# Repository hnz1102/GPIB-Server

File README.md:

<div align="center">
  <h1><code>GPIB Server</code></h1>
  <p>SSH / Web controlled IEEE-488 (GPIB) controller on a single ESP32-S3</p>
  
</div>

# gpib-server — SSH-to-GPIB Bridge for ESP32-S3

Firmware for the ESP32-S3 **GPIB-Server** board. It drives an IEEE-488 (GPIB)
bus directly from GPIO through SN75160B / SN75161B bus transceivers. Measuring
instruments can be controlled over Wi-Fi with an **SSH** session or the
**browser terminal**, using **Prologix-compatible** `++` commands.

It is written in Rust (esp-idf-hal / esp-idf-svc), with a C component (wolfSSH)
for the SSH server. It is derived from
[ssh-serial-bridge](#release-history) v0.1.2.

## Features

| Feature | Description |
|---------|-------------|
| GPIB controller | System controller / controller-in-charge on the GPIB bus (IFC, REN, ATN, SRQ, serial poll, SDC, GET, GTL, LLO) |
| Prologix-compatible commands | `++addr`, `++read`, `++auto`, `++eos`, `++eoi`, `++spoll`, `++clr`, `++trg` … (controller mode) |
| SSH server | Port 22, password authentication via wolfSSH, interactive (`gpib`) and script (`gpib raw`) modes |
| WebSocket terminal | Built-in xterm.js GPIB terminal at `/terminal` |
| Spectrum view | Real-time trace display of an ADVANTEST R3267 (R3200 series) spectrum analyzer at `/spectrum` (binary capture on the ESP32, ~13 frames/s) |
| Power supply page | Control and monitoring of an HP / Agilent 6612B (SCPI) DC power supply at `/psu`: output, set values, protection, trend chart, CSV |
| Multimeter page | HP / Agilent 34401A digital multimeter at `/dmm`: function, range, resolution, null, statistics, trend chart, CSV |
| Web UI | Browser-based configuration and device status (GPIB address, SRQ, SSH sessions) |
| Mini display | SSD1306 128×64 OLED (I2C): Wi-Fi, IP, GPIB address, chip temperature |
| WPS support | Wi-Fi Protected Setup (PBC mode) |
| OTA update | `ssh … update < app.bin` with automatic rollback |
| UDP Syslog | RFC 5424 remote logging over UDP |
| NTP | Time synchronisation on boot; up to 4 servers |
| NVS settings | Persistent configuration stored in NVS; editable via Web UI at runtime |

---

## Screenshots

<table>
<tr>
<td align="center" width="50%"><br><b>Main menu</b> (<code>/</code>)</td>
<td align="center" width="50%"><br><b>GPIB terminal</b> (<code>/terminal</code>)</td>
</tr>
<tr>
<td align="center"><br><b>DC power supply</b>, HP 6612B (<code>/psu</code>)</td>
<td align="center"><br><b>Digital multimeter</b>, HP 34401A (<code>/dmm</code>)</td>
</tr>
<tr>
<td align="center"><br><b>Status</b> (<code>/status</code>)</td>
<td align="center"><br><b>Configuration</b> (<code>/config</code>)</td>
</tr>
<tr>
<td align="center" colspan="2"><br><b>Login</b> (<code>/login</code>)</td>
</tr>
</table>

The power supply and multimeter screenshots were taken with simulated instrument
replies; the other pages show the live device (Wi-Fi name and passwords replaced).

## Release History

### v0.1.0 (gpib-server)

- First GPIB-Server release, derived from ssh-serial-bridge v0.1.2.
- Added the GPIB controller driver and the Prologix-compatible command interpreter (`src/gpib.rs`).
- Added the SSH `gpib` / `gpib raw` commands and the browser GPIB terminal.
- Removed UART (COM1/COM2), USB CDC host, GPIO/PWM outputs, SPI display, ADC / power detection and the related SSH commands (`console usbN/comN`, `power`, `dcpower`, `powercycle`, `pwm`).
- Moved the mini display SDA to GPIO13.
- The console log now goes to USB-C (USB-Serial-JTAG).

---

## Architecture

```
SSH client ──[TCP:22]──► ssh_bridge.c (wolfSSH)
                               │  per-session ring buffers (PSRAM)
                               ▼
                        bridge.rs (SSH / WebSocket glue)
                               │
Browser ──[HTTP/WS]──► httpserver.rs ──► gpib.rs
 ├── /          (configuration page)      ├── Prologix-compatible interpreter (worker thread)
 └── /terminal  (xterm.js + /ws/serial)   └── GPIB bus driver (GPIO, 3-wire handshake)
                                                 │
                         SN74LVC245A ×2 ── SN75160B / SN75161B ── GPIB connector
```

---

## Hardware

<table>
<tr>
<td align="center" width="33%"><br><b>PCB</b>: SN75160B / SN75161B transceivers, SN74LVC245A buffers, USB-C, BOOT/CFG button and SSD1306 OLED; the IEEE-488 connector is on the back</td>
<td align="center" width="33%"><br><b>Case</b> (3D-printed): USB-C power on the left, GPIB connector on the right</td>
<td align="center" width="33%"><br><b>Mini display</b>: Wi-Fi RSSI, IP address, GPIB address and chip temperature</td>
</tr>
</table>

### Case (3D printing)

| File | Part | Size (W × D × H) |
|------|------|------------------|
| [`hw/body.stl`](hw/body.stl) | Body | 86 × 67 × 25 mm |
| [`hw/upper.stl`](hw/upper.stl) | Upper part | 91 × 76 × 27 mm |

Sizes are the bounding boxes of the STL files.

The schematic is in [`hw/GPIB-Server.kicad_sch`](hw/GPIB-Server.kicad_sch) ([PDF](hw/schematic.pdf)). For the
design rationale (level translation, direction control and pull-ups), see
[`doc/gpib-hardware.md`](doc/gpib-hardware.md).

| Ref | Part | Function |
|-----|------|----------|
| U1 | ESP32-S3-WROOM-1-N16R8 | MCU (16 MB flash, 8 MB octal PSRAM) |
| U2 | AZ1117-3.3 | 5 V (USB VBUS) → 3.3 V LDO |
| U3 | SSD1306 module | 128×64 OLED (I2C) |
| U4 | SN74LVC245A | DIO1–8 buffer (3.3 V, 5 V-tolerant) |
| U5 | SN74LVC245A | DAV / EOI / NRFD / NDAC buffer (NRFD/NDAC wired B→A reversed) |
| U6 | SN74LVC1G34 | SRQ input buffer |
| U7 | SN75160B | GPIB data transceiver (5 V) |
| U8 | SN75161B | GPIB management transceiver (5 V, DC = GND → system controller) |
| J1 | USB-C (device) | 5 V power, flashing and console (USB-Serial-JTAG) |
| J2 | IEEE-488 24-pin | GPIB connector |

### Pin Assignment

| GPIO | Signal | Direction (ESP32 side) | Path |
|------|--------|------------------------|------|
| 4–11 | DIO1–DIO8 | bidirectional (TE) | U4 → U7 |
| 15 | DAV  | bidirectional (same as TE) | U5 A1/B1 → U8 |
| 18 | EOI  | bidirectional (same as TE) | U5 A2/B2 → U8 |
| 16 | NRFD | bidirectional (inverse of TE) | U5 B3/A3 (reversed) → U8 |
| 17 | NDAC | bidirectional (inverse of TE) | U5 B4/A4 (reversed) → U8 |
| 21 | ATN  | output | 1 kΩ → U8 |
| 38 | REN  | output | 1 kΩ → U8 |
| 39 | IFC  | output | 1 kΩ → U8 |
| 40 | SRQ  | input  | U8 → U6 |
| 12 | TE   | output (direction: H = talk) | U7/U8 TE, U4/U5 DIR (10 kΩ pull-down) |
| 2  | OE#  | output (LVC245A enable, active low) | U4/U5 OE (10 kΩ pull-up) |
| 13 | I2C SDA | — | OLED |
| 3  | I2C SCL | — | OLED |
| 0  | BOOT button | input | Long press (≥ 10 s): factory reset |
| 46 | (strap) | — | 10 kΩ pull-down (download mode works with the BOOT button) |
| 19 / 20 | USB D− / D+ | — | USB-C (USB-Serial-JTAG) |

The GPIB bus uses negative logic: a LOW level means asserted, and a data bit of 1
is driven LOW. The firmware handles the inversion.

### Button

| GPIO | Function |
|------|----------|
| 0 (BOOT) | Long press (≥ 10 s): erase NVS and restore `cfg.toml` defaults. A countdown is shown on the mini display from 5 s onwards. |

---

## Directory Layout

```
gpib-server/
├── src/
│   ├── main.rs           # Entry point, peripheral initialisation
│   ├── gpib.rs           # GPIB bus driver + Prologix-compatible interpreter
│   ├── bridge.rs         # SSH (C component) / WebSocket ⇄ GPIB glue
│   ├── httpserver.rs     # HTTP/WebSocket server, NVS config management
│   ├── wifi.rs           # Wi-Fi STA connection (DHCP / static IP / WPS)
│   ├── mini_display.rs   # SSD1306 status display
│   ├── syslogger.rs      # UDP Syslog logger (RFC 5424)
│   ├── btn_ctrl.rs       # GPIO0 button (long press: factory reset)
│   └── boot_log.rs       # NVS boot counter and rolling reset-reason log
├── components/
│   ├── ssh_bridge/       # SSH server C component (wolfSSH wrapper)
│   ├── wolfssh/          # wolfSSH (github.com/wolfSSL/wolfssh, commit 157cb01f)
│   └── wolfssl/          # wolfSSL/wolfCrypt (github.com/wolfSSL/wolfssl, commit b7e7e755)
├── doc/gpib-hardware.md  # Hardware design notes (pin list, connections, rules)
├── hw/
│   ├── GPIB-Server.kicad_* # KiCad project, schematic and PCB
│   ├── schematic.pdf     # Schematic (PDF)
│   ├── production/       # Gerber (zip), BOM, positions, netlist for PCB assembly
│   ├── body.stl          # Case: body (3D printing)
│   └── upper.stl         # Case: upper part (3D printing)
├── static/               # Embedded pages and files (menu, status, spectrum, psu, dmm; xterm.js (gzip) / css / fit addon)
├── cfg.toml.example      # Template for cfg.toml (build-time defaults; cfg.toml itself is not in git)
├── sdkconfig.defaults    # ESP-IDF build settings
├── partitions.csv        # Flash partition table
├── setup_components.sh   # Initial setup script for components/
└── setup_env.sh          # One-shot environment setup (Rust, espup, udev)
```

---

## Configuration

### cfg.toml (build-time defaults)

Copy `cfg.toml.example` to `cfg.toml` and edit it for your environment before
building (`cfg.toml` holds credentials and is ignored by git). The section name must
match the crate name (`gpib-server`).

```toml
[gpib-server]
wps_enable     = "true"     # "true": use WPS PBC on next boot when SSID is empty
wifi_ssid      = "your-ssid"
wifi_psk       = "your-password"
ip_mode        = "dhcp"           # "dhcp" or "static"
ip_address     = "192.168.0.200"
subnet_mask    = "255.255.255.0"
gateway        = "192.168.0.1"
dns            = "1.1.1.1"

syslog_server    = "192.168.0.140:514"
syslog_enable    = "false"
syslog_host_name = "gpib-server"
syslog_app_name  = "gpib-server"

ssh_user     = "admin"
ssh_password = "gpibpass"

# NTP servers (up to 4, in priority order)
ntp_server1 = "time.aws.com"
ntp_server2 = "time.google.com"
ntp_server3 = "time.cloudflare.com"
ntp_server4 = "ntp.nict.jp"

mini_display_enable = "true"      # SSD1306 OLED (U3)

gpib_addr = "1"      # terminal / SSH (++addr) address at power-up
sa_addr   = "30"     # ADVANTEST R3267 (/spectrum)
psu_addr  = "2"      # HP 6612B (/psu)
dmm_addr  = "22"     # HP 34401A (/dmm)
```

Values in `cfg.toml` are compiled into the firmware as defaults.
After boot they can be overridden via the Web UI; NVS values take priority.

### GPIB addresses

The four `*_addr` keys are defaults (0–30). They are stored in NVS when changed:

- **Configuration page → GPIB**: all four addresses. "Save to NVS" stores them;
  `gpib_addr` (the address selected at power-up for `++` commands) takes effect
  after a reboot.
- **ADDR field on /spectrum, /psu, /dmm**: changing it saves that instrument's
  address to NVS immediately (`POST /api/gpib_addr`), so every browser opens the
  page with the same address.

`++addr` in a terminal / SSH session changes the address only for the running
session and is not saved. Other GPIB settings (EOS, timeouts …) are not stored in
NVS either; set them with `++` commands, as on a Prologix adapter. Reset Defaults
(or the 10 s BOOT-button press) returns all addresses to the `cfg.toml` values.

---

## Wi-Fi Setup with WPS

The device supports **WPS Push Button Configuration (PBC)**.

1. In `cfg.toml`, set `wifi_ssid = ""` and `wps_enable = "true"`. Alternatively,
   clear the SSID and enable WPS in the Web UI, then reboot.
2. Flash the firmware (or reboot).
3. On boot, the device enters WPS mode and the mini display shows
   **"WPS MODE"**. Press the **WPS button on your router** within 2 minutes.
4. On success, the credentials are saved to NVS ("WPS SUCCESS" → "CONNECTED").

To return to WPS mode on a configured device, perform a **factory reset**: hold
the BOOT button (GPIO0) for **≥ 10 seconds**. This restores the `cfg.toml`
defaults, so WPS starts if `cfg.toml` has an empty SSID.

If WPS fails or times out, the device falls back to the configured credentials.
Only PBC mode is supported (PIN mode is not).

---

## Environment Setup

Run `setup_env.sh` **once** on a fresh Ubuntu / Debian machine (or WSL2) before
building.

```bash
bash setup_env.sh
source "$HOME/.cargo/env"
source ~/export-esp.sh
```

| Step | Action |
|------|--------|
| 1 | Install system packages via `apt` |
| 2 | Install Rust toolchain via `rustup` (skipped if already present) |
| 3 | Install `ldproxy`, `espup`, `cargo-espflash` via Cargo |
| 4 | Install & update the ESP32-S3 Xtensa toolchain via `espup` |
| 5 | Source `~/export-esp.sh` (generated by `espup`) |
| 6 | Add udev rule for ESP32 USB device (`303a:1001`) and reload rules |

---

## Build and Flash

### Initial component setup

Run this once after cloning, after a clean wipe of `components/`, or after moving
the checkout. The last case matters because it rewrites the absolute
partition-table path in `sdkconfig.defaults`.

```bash
bash setup_components.sh
```

### Build

```bash
cargo build --release
```

### Flash and monitor (USB-C)

Connect the board's USB-C port to the PC. The ESP32-S3 appears as a
USB-Serial-JTAG device (`303a:1001`), which is used for both flashing and the
log console.

```bash
espflash flash --release --monitor
```

If the device does not enter download mode automatically, hold **BOOT**, press
reset (or re-plug USB), then release BOOT.

### Images for distribution / OTA

```bash
# Merged full-flash image (write at offset 0x0)
cargo espflash save-image --release --merge --chip esp32s3 flash_images/flash_gpib-server.bin

# App-only image for `ssh … update` (OTA)
cargo espflash save-image --release --chip esp32s3 flash_images/app_gpib-server.bin
```

Always write the merged image at **offset 0x0**:

```bash
espflash write-bin 0x0 flash_images/flash_gpib-server.bin
```

### Flash layout

| Partition     | Offset   | Size    |
|---------------|----------|---------|
| nvs           | 0x9000   | 24 KB   |
| otadata       | 0xF000   | 8 KB    |
| phy_init      | 0x11000  | 4 KB    |
| ota_0 (app)   | 0x20000  | 4032 KB |
| ota_1 (app)   | 0x410000 | 4032 KB |

Flash: 8 MB layout, DIO mode, 40 MHz. The N16R8 module has 16 MB of flash;
the upper 8 MB are currently unused.

---

## SSH Connection

| Item | Detail |
|------|--------|
| Port | 22 (TCP) |
| Auth method | Password only (public-key authentication is not supported) |
| Username | Any string is accepted — only the password is checked |
| Password | `ssh_password` in `cfg.toml` or Web UI |
| Concurrent sessions | Up to 6 total; up to 4 sessions can share the GPIB console |

> **Security note:** Change the default password before you put the device on a
> shared network. Remote control of instruments such as power supplies can be
> hazardous.

### Commands

| Command | Description |
|---------|-------------|
| `ssh -tt <user>@<ip> gpib` | Interactive GPIB console (local echo, auto-read after each line) |
| `ssh <user>@<ip> gpib raw` | Prologix-style raw console (no echo, `++auto 0`) for scripts |
| `ssh -tt <user>@<ip> console gpib` | Alias of `gpib` |
| `ssh <user>@<ip> reboot` | Reboot the ESP32-S3 |
| `ssh <user>@<ip> update < app.bin` | OTA firmware update |

Disconnect an interactive session with **Enter**, then **`~.`**

### Interactive example

```
$ ssh -tt admin@192.168.0.200 gpib
Connected to ESP32-S3 GPIB-Server v0.1.0 [gpib].
Type ++help for commands. Disconnect: Enter then ~.

++addr 22
*IDN?
KEITHLEY INSTRUMENTS INC.,MODEL 2000,...
:MEAS:VOLT:DC?
+1.23456789E+00
++spoll
0
```

In interactive mode, every line that does not start with `++` is sent to the
instrument (with the EOS terminator). The response is then read automatically,
up to EOI or LF. Error messages (timeouts, no listener …) are printed only in
interactive mode.

### Prologix-compatible commands

| Command | Description | Default |
|---------|-------------|---------|
| `++addr [pad [sad]]` | Get/set instrument address (pad 0–30, sad 96–126) | `gpib_addr` (1) |
| `++auto [0\|1]` | Read automatically after each write | 1 interactive / 0 raw |
| `++clr` | Selected Device Clear (SDC) | |
| `++eoi [0\|1]` | Assert EOI with the last byte of writes | 1 |
| `++eos [0-3]` | Write terminator: 0 = CR+LF, 1 = CR, 2 = LF, 3 = none | 2 |
| `++eot_enable [0\|1]` | Append `eot_char` to read data when EOI is seen | 0 |
| `++eot_char [0-255]` | Character appended when `eot_enable` = 1 | 10 |
| `++ifc` | Interface Clear | |
| `++llo` | Local Lockout | |
| `++loc` | Go To Local (GTL) for the current address | |
| `++mode [1]` | Controller mode only (always 1) | 1 |
| `++read [eoi\|<char>]` | Read until EOI, `<char>` (decimal) or timeout | |
| `++read_tmo_ms [ms]` | Read / handshake timeout, 1–60000 ms | 3000 |
| `++rst` | Re-initialise the GPIB bus (IFC + REN) | |
| `++spoll [pad [sad]]` | Serial poll; returns the status byte | |
| `++srq` | SRQ line state (1 = asserted) | |
| `++trg [pad …]` | Group Execute Trigger (GET) | |
| `++ver` | Version string | |
| `++help` | Command list | |
| `++echo [0\|1]` | *(extension)* local echo / CRLF conversion | 1 interactive / 0 raw |
| `++ren [0\|1]` | *(extension)* REN line | 1 |
| `++savecfg` | Accepted for compatibility (no effect) | |

To send CR, LF, ESC or `+` as data, prefix the character with ESC (0x1B).

Not supported: device mode (`++mode 0`, `++lon`, `++status`) and parallel poll.

### Scripting

`gpib raw` behaves like a Prologix adapter. Send `++` commands and data lines
to stdin, and read the responses from stdout:

```bash
ssh admin@192.168.0.200 gpib raw
++addr 22
*IDN?
++read eoi
```

To use the device from software that speaks the Prologix-over-TCP protocol (for
example, PyVISA with pyvisa-py's Prologix support), expose the SSH session as a
local TCP port:

```bash
socat TCP-LISTEN:1234,reuseaddr,fork EXEC:"ssh admin@192.168.0.200 gpib raw"
```

> When stdin reaches EOF, the session may close before a pending response
> arrives. For one-shot pipes, keep stdin open until the reply has been read
> (for example, use `socat` or an interactive client).

### OTA firmware update

```bash
cat flash_images/app_gpib-server.bin | ssh admin@192.168.0.200 update
```

- Use the **app-only** image, not the merged image.
- The update is written to the inactive OTA slot. The new image is marked valid
  once the SSH server starts; otherwise the bootloader rolls back on the next
  reset.

---

## Web UI

| URL | Method | Description |
|-----|--------|-------------|
| `/login` | GET / POST | Login (same user / password as SSH) |
| `/logout` | GET | Logout |
| `/` | GET | Main menu: Status, Spectrum Analyzer, DC Power Supply, Configuration, GPIB terminal, logout (auth required) |
| `/status` | GET | Device status (IP, Wi-Fi, chip temperature, uptime, GPIB, spectrum capture, SSH sessions) and boot / diagnostic log (auth required) |
| `/config` | GET | Configuration page: Wi-Fi, network, Syslog, authentication, NTP; save / defaults / reboot (auth required) |
| `/terminal` | GET | Browser GPIB terminal (auth required) |
| `/spectrum` | GET | R3267 real-time spectrum view (auth required) |
| `/psu` | GET | DC power supply (HP 6612B) control page (auth required) |
| `/dmm` | GET | Digital multimeter (HP 34401A) page (auth required) |
| `/ws/serial` | WS | Terminal data (`{"cmd":"init","port":"gpib","token":…}`, then binary frames) |
| `/ws/spectrum` | WS | Spectrum control (`{"cmd":"start"\|"stop",…}`) and trace frames |
| `/ws/inst` | WS | Instrument-page requests (`{"cmd":"req","dev":"psu"\|"dmm","addr":2,"q":"VOLT 5\|MEAS:VOLT?",…}`) and replies |
| `/api/config` | POST | Save configuration to NVS |
| `/api/gpib_addr` | POST | Save an instrument page's address to NVS (`dev=sa\|psu\|dmm&addr=0..30`) |
| `/api/status` | GET | IP / Wi-Fi / chip temperature / GPIB address / SRQ / SSH sessions / spectrum running / uptime (JSON) |
| `/api/reset` | POST | Erase NVS and restore cfg.toml defaults |
| `/api/reboot` | POST | Reboot the device |
| `/api/boot_log` | GET | Boot history with reset reasons (JSON) |
| `/api/diag_log` | GET | Diagnostic entries stored in NVS (JSON) |

After login the **main menu** opens. Each page (status, spectrum view, power
supply, configuration, terminal) has a **← Main menu** button that returns to it.

The browser terminal behaves like the interactive SSH console (echo +
auto-read). It shares the GPIB interpreter with any SSH sessions.

**Language.** Every page (login, configuration, terminal, spectrum view) can be
shown in English or Japanese. Use the **EN | 日本語** switch in the page header.
The choice is stored in the browser (localStorage); the default follows the
browser language. Hover help and messages follow the same setting. The R3267
front-panel key names (FREQ, Center, Ref Level, …) stay in English, as on the
instrument.

Login sessions are held in RAM only, so they become invalid when the ESP32
restarts. Every page then shows a **"Session expired"** notice with a **Reload**
button, triggered by HTTP 401 from `/api/*` or by `{"type":"auth","error":…}`
on the WebSocket. Reloading leads to the login page.

WebSocket messages must carry the login session token. The `/terminal`,
`/spectrum`, `/psu` and `/dmm` pages embed it, and messages with a missing or wrong token are ignored.

### Power supply page (`/psu`)

Controls an **HP / Agilent 6612B** system DC power supply (20 V / 2 A, SCPI) on
the GPIB bus. Commands follow the Agilent programming guide 5962-8198, which
covers 66312A / 6631B–6634B / 6611C–6614C; the 6612B uses the same platform. Other
models of that family work too, because the limits are read from the instrument.
The default address is **2** (`psu_addr`); a changed address is saved to NVS.
Open the page from **DC Power Supply** in the main menu.

| Area | Function | SCPI |
|------|----------|------|
| Output (measured) | Voltage, current (mA below 20 mA), power; mode badges CV / CC; protection badges OV / OCP / OT / FS / RI / UNREG / OVLD | `MEAS:VOLT?` `MEAS:CURR?` `STAT:OPER:COND?` `STAT:QUES:COND?` |
| | **OUTPUT ON / OFF** | `OUTP ON\|OFF` |
| | **Clear protection** (blinks when a protection has tripped) | `OUTP:PROT:CLE` |
| Settings | Voltage, current limit: value + **Set** (or Enter), − / + by the selected step | `VOLT` `CURR` |
| | OVP level, OCP (output off on CC), protection delay | `VOLT:PROT` `CURR:PROT:STAT` `OUTP:PROT:DEL` |
| Data entry | **Keypad** and **jog dial** for the active setting (Voltage / Current / OVP / Delay; also selected by clicking a setting name). Type a value and press **V/A/s** or **ENT** (or **mV/mA/ms** for milli units). ▲ ▼ and the jog dial change it by the step; ÷10 / ×10 change the step; Shift = 10 × step | `VOLT` `CURR` `VOLT:PROT` `OUTP:PROT:DEL` |
| Measurement | Current range High / Low 20 mA, points × interval (measurement time shown) | `SENS:CURR:RANG` `SENS:SWE:POIN` `SENS:SWE:TINT` |
| State memory | Save / recall states 0–3 (with confirmation), reset, clear status | `*SAV` `*RCL` `*RST` `*CLS` |
| | Error log | `SYST:ERR?` (read on every update) |
| Trend | Voltage (green) and current (yellow) against time; CC / OFF periods are shaded. **CSV** downloads every sample (time, V, A, W, mode) | — |
| Toolbar | Update interval 0.5 / 1 / 2 / 5 s or **Pause**; **Local** = Go To Local | GTL |

- Keyboard: 0-9 and `.` type a value, Enter sets it, `m` sets it in milli units,
  Backspace / Esc edit; ↑ → / ↓ ← = jog (Shift = coarse). These keys work when no
  input field has the focus. Jog ticks are combined and sent at most about 7 times
  per second, each as one absolute value (e.g. `VOLT 5.3`). The step of each
  setting and the active setting are stored in the browser.
- Set values are limited to the model maxima (`VOLT? MAX`, `CURR? MAX`,
  `VOLT:PROT? MAX`; 6612B: 20.475 V, 2.0475 A, OVP 22 V). Programming a voltage at
  or above the OVP level shows a warning, because OVP would trip.
- While the page polls, the instrument stays in remote and its front panel is
  locked. To use the front panel, press **Local**, which also sets Update to Pause.
- One request runs at a time: commands, then the setting queries, then the
  measurements. The ESP32 accepts only the commands listed above
  (`gpib::validate_psu_item`). Other SCPI commands can be sent from the terminal
  (`++addr 2`).
- Requests are interleaved with the spectrum view on the same bus, so both
  pages can be open at once.
- Tested with a 6612B (firmware A.00.05). It does not support `SENS:WIND`
  (error -113), so the page has no window setting.
- The R3267 also uses address 30 by default. Give each instrument its own address.

### Multimeter page (`/dmm`)

Controls an **HP / Agilent 34401A** 6½-digit multimeter. Commands follow the
34401A User's Guide, chapter 4 (Remote Interface Reference). The default address
is **22** (`dmm_addr`); a changed address is saved to NVS. Open the page from
**Digital Multimeter** in the main menu.

| Area | Function | SCPI |
|------|----------|------|
| Reading | Value in the front-panel format: the range sets the prefix and the number of digits. **OVLD** for 9.9E+37 (**OPEN** in continuity / diode). Annunciators AUTO / MAN / NULL / AZ / HI-Z / FRONT·REAR / OVLD | `READ?` `CONF?` |
| | **Run** (continuous), **Hold**, **Single**; interval Fast / 0.5–10 s; readings per second shown | `READ?` |
| Function | DC V, AC V, DC I, AC I, Ω 2W, Ω 4W, Freq, Period, Continuity, Diode | `CONF:…` |
| Range | AUTO or a fixed range of the function (100 mV … 1 kV, 10 mA … 3 A, 100 Ω … 100 MΩ); Freq / Period: input voltage range | `<func>:RANG` `<func>:RANG:AUTO` |
| Resolution | DC / Ω: NPLC 0.02 / 0.2 / 1 / 10 / 100 (4½ … 6½ digits, integration time shown); AC: filter 3 / 20 / 200 Hz; Freq / Period: gate time 10 ms / 100 ms / 1 s | `<func>:NPLC` `DET:BAND` `FREQ:APER` `PER:APER` |
| Options | Null (the next reading becomes the offset), autozero ON / OFF / ONCE, input resistance 10 MΩ / >10 GΩ, beeper, front display | `CALC:FUNC NULL` `CALC:STAT` `ZERO:AUTO` `INP:IMP:AUTO` `SYST:BEEP:STAT` `DISP` |
| | Reset, clear status, error log | `*RST` `*CLS` `SYST:ERR?` |
| Statistics | Mean, min, max, standard deviation, peak-to-peak, count, computed in the browser (reset when the function changes) | — |
| Trend | Readings against time with the mean line; **CSV** downloads every reading (time, value, unit, function, range) | — |

- Each cycle sends `READ?` and then `CONF?`, so the displayed range follows
  autoranging. `CONFigure` sets the trigger source to IMMEDIATE, so `READ?`
  measures at once.
- A reading at 100 NPLC with autozero takes about 3.5 s, so the bus timeout for
  the multimeter is 12 s. During a reading the bus is busy; spectrum frames and
  power-supply requests wait for it.
- The meter stays in remote (Rmt) while the page measures. **Local** stops the
  measurement and sends Go To Local.
- The front / rear terminal switch cannot be set over GPIB; the page only shows it.

### Spectrum view (`/spectrum`)

The page shows a real-time trace from an **ADVANTEST R3267** (R3200-series
GPIB codes). Enter the GPIB address, CENTER [MHz], SPAN [MHz] and RBW [kHz], then
press **Start**. The ESP32 then:

1. sends `DL2` (delimiter = EOI only) and reads back the settings
   (`CF? SP? RB? FA? FB? RL? DD? TP? VB? SW? AT? CS?`, the AUTO flags, and `MN? MF? ML?`);
2. repeats `TS` (take sweep, waits for completion) + `TBA?` (trace A, binary,
   2 bytes × 501/1001 points, high byte first), and pushes each frame to the browser;
3. re-reads the settings every 15 frames and after each panel command, so changes made on the real front panel are picked up too;
4. restores `DL0` (CR LF EOI) on **Stop**, or when the last viewer closes the page.

Press **Start** to capture with the instrument's current settings.

**Front panel (right side).** The panel works like the R3267 front panel:

| Part | Function |
|------|----------|
| REPEAT / SINGLE | REPEAT: continuous capture (`CONTS`). SINGLE: the ESP32 captures one sweep per press, then holds the display (`SNGLS`) |
| Function keys | FREQ / SPAN / LEVEL / ATT / COUPLE / SWP / TRACE A / TRACE B / FORMAT / WINDOW / MKR / SRCH / MKR→ / MEAS / POWER / UTIL / CAL / CONFIG / SAVE / RCL / PRESET — the GPIB-controllable functions of R3267 Operation Manual Vol.1 tables 5-1 … 5-21 |
| Soft keys | Change with the selected function and show the current values and states, for example TRACE A: Write / View / Blank, Max / Min Hold, Average, Sweep Count, Detector, Clear |
| Numeric keys + unit keys | Type a value, then press a unit (GHz/MHz/kHz/Hz, dBm/dB, s/ms/µs, ENTER) to send it |
| Jog dial | Mouse wheel over the dial, the value display or the graph, or drag the dial: fine steps of the active function (hold Shift for coarse steps). Ticks are batched, about 10 commands/s at most |
| ↑ / ↓ | Coarse steps (1-2-5 / 1-3 sequences, CF step, dB/div) |
| Click on the graph | Move the instrument marker there (`MK …`) |
| PC keyboard | Digits, `.`, `-`, Backspace, Esc (clear), Enter (default unit), ↑ / ↓ (coarse), ← / → (jog) |

Soft-key states (ON/OFF, selections, values such as Min ATT) are read with
read-only panel queries when a menu opens, after each key, and every 4 s.
Measurement results are polled every 1.5 s while their mode is on, and shown in
the **RESULT** box. Examples: OBW / Fc, channel / total / average power, ACP,
counter, noise/Hz, %AM, harmonics, C/N, phase jitter, IM, pass/fail,
XY cursor Δ.
List results (ACP, harmonics, C/N, IM) are shown as tables. Each
column has one unit, given in its header, and fixed decimals, so the digits line up.
The `#` column matches the numbered markers on the graph.
With W / V units the graph switches to a linear scale (0 … reference level). In
zero span the X axis, results and marker are shown as time.

Not available from the panel: table entry (limit, correction, CS/BS, spurious and
offset tables), label text, printer / bitmap / file / memory-card operations,
external-mixer functions (R3273 only), and writing the 10 MHz reference
calibration values. PRESET, RCL, SAVE / DEL and the calibrations ask for
confirmation.

The graph shows trace A (green), trace B (magenta, when it is not Blank), the
display line (FORMAT, orange), the instrument marker and the peak.
**Peak list.** The **PEAK LIST** box (below REPEAT / SINGLE) finds the peaks in the
browser, in every captured frame, so the list follows the signal at the frame rate
without extra GPIB traffic. **Level** lists the largest peaks first, **Freq** in
frequency order; **Off** turns it off. Settings (kept in the browser):

| Setting | Meaning |
|---------|---------|
| Trace | Trace A, trace B or the browser max hold |
| Excursion | A peak must rise at least this much (dB) above the lowest point on each side before a higher point (its prominence). Default 6 dB |
| Threshold | Peaks below this level are ignored. Empty = auto: noise floor (median of the trace) + 10 dB |
| Max | Number of peaks listed (1–50, default 10) |
| Labels | Frequency / level label next to each marker |

The table shows each peak's frequency (time in zero span), level, difference to
the largest peak and Δf. The table always has Max rows (blank rows pad a short list; over 10
rows it scrolls), so its height does not change and the keys below stay in place. The peaks are drawn as numbered yellow ▼ markers; labels
that would overlap are left out. Hovering a row highlights its marker with a guide
line; clicking a row moves the instrument marker to that peak (`MK`). The level is
the trace point (no interpolation), as on the instrument display.

The instrument's own peak list (**MKR → Peak List Freq / Level**, `PLS`, `PKLST?`)
is still available. Its markers are shown when the browser list is Off. The R3267
searches only once, when `PLS` is sent, and does not re-sort the list afterwards.
The peak list is also written to the CSV header. The R3267 has no query for the peak-list state,
and `PKLST?` keeps returning the last list after `PLS OFF`. So the page tracks the
state itself: Peak List Freq / Level turns it on, and Peak List OFF, Marker OFF,
PRESET and RCL turn it off. If the peak list is switched on or off on the instrument's
own front panel, the page does not see it.
The **XY cursor** (TRACE A → XY Cursor) is drawn as white dotted X / Y lines
(`XYCSR?`, `CSRX?`, `CSRY?`, read every 3 s and shortly after a cursor key). When an
anchor is set (Set Anchor / `SETANC`), it is drawn as an orange ⊕, and ΔX / ΔY are
shown at the cursor crossing. There is no query for the anchor itself:
`CSRDX?` / `CSRDY?` return the offset from the anchor, or −999999999 when no anchor
is set. So the anchor position is `CSRX − CSRDX`, `CSRY − CSRDY`.
The **peak search condition** (SRCH) has all of its GPIB settings:
- X range All / Inner / Outer, with the search window position and width
  (`MKSPOS`, `MKSWID`) and Couple to F (`MKSCPL`).
- Y range All / display line / limit line, with Above or Below for the display
  line and limit lines 1 and 2 (`MKSYDL`, `MKSYLA`, `MKSYLB`).

The search window is drawn in violet, shaded inside for Inner and outside for
Outer. With Y: Disp Line, the searched side of the display line is shaded.

**Saving (toolbar).** The browser saves the data it already has, so this works
while capturing and needs nothing from the instrument:

| Button | File | Content |
|--------|------|---------|
| ⬇ CSV | `r3267_YYYYMMDD_HHMMSS.csv` | One row per point: `freq_Hz` (or `time_s` in zero span), trace A, trace B (if not Blank), browser max hold (if on), and the lower screen of a split display. `#` header lines hold the settings (CF, span, RBW, VBW, sweep time, ATT, REF, scale, unit, trace modes, detector), the marker, the XY cursor / anchor and the peak list |
| ⬇ PNG | `r3267_YYYYMMDD_HHMMSS.png` | The graph as shown (spectrum, lower screen, waterfall) with a settings line |
| ● REC | `r3267_rec_YYYYMMDD_HHMMSS.csv` | Records every trace-A frame until pressed again: one row per frame (`time` ISO 8601, `elapsed_s`, the level at each point). The first row holds the frequencies. Stops and saves by itself when the frequency axis or level scale changes, or after 20000 frames |

Read the CSV with, for example, `pandas.read_csv(f, comment="#")`.

**Split screen (WINDOW Zoom / F/T / T/T).** The graph splits into an upper and
a lower pane, each with its own axes (for example frequency domain above and
time domain below in F/T). The R3267 sends only the selected screen over GPIB,
so each frame does `SCRSEL TRA` → `TS` → `TBA?` and `SCRSEL TRB` → `TS` → `TBA?`, then
selects the screen the user chose again. The lower screen's settings are sent as
a separate `meta2` message and its trace as frame tag `C`. A pane tag shows which
screen is selected for settings ("◀ active"). Each `SCRSEL` switch takes about
0.4 s, so the update rate drops to about 1 frame/s. With the waterfall on, the
graph area is divided 36 / 28 / 36 %; the waterfall shows the upper screen.

The ESP32 accepts only the panel codes listed in `PANEL_CODES` (`src/gpib.rs`), each
with its allowed argument form: none, `<number><unit>`, or a keyword such as `ON`,
`OFF`, `NRM`, `VIDEO`. Anything else is rejected, for example `DL0`, `TBA` or
`PRESET`. Commands that arrive while a frame is being captured are processed as one
batch, followed by a single full read-back of the settings. A light refresh of the
main values runs every 15 frames.

**Interrupting.** Stop (or Start), Ctrl-C in an interactive SSH or browser-terminal
session, and any panel key pressed while a frame has been stuck for more than 1 s
abort the bus operation in progress. The bus is then reset with IFC.

> **Trigger caution:** with Video / Ext trigger and no trigger signal, a pending
> `TS` (take sweep) makes the R3267 refuse all GPIB data. IFC and Device Clear do
> not help; only the front panel or a power cycle releases it. The capture
> therefore sends `TS` only in Free Run. With other trigger sources it just reads
> the current trace.

The browser converts the raw values with `level = RL + (raw − 14592) / 1280 × dB/div`
(R3267 Operation Manual Vol.1, 5.2.10.3). It draws the trace with a peak marker,
a cursor readout and optional max hold.

While the spectrum view runs, the GPIB bus is shared with SSH and terminal
sessions, so their commands are interleaved between frames. The R3267 delimiter
is `DL2` during capture, so ASCII replies end with EOI only (no CR LF).

For PC-side capture to CSV, see [`tools/r3267_capture.py`](tools/r3267_capture.py).

---

## Dependencies

| Component / Library | Version | License | Purpose |
|---------------------|---------|---------|---------|
| **gpib-server** (this project) | 0.1.0 | MIT | Firmware (Rust) |
| **ssh_bridge** component | 0.1.0 | MIT | SSH server C wrapper |
| esp-idf-hal | 0.45 | MIT / Apache-2.0 | ESP32-S3 hardware abstraction |
| esp-idf-svc | 0.51 | MIT / Apache-2.0 | Wi-Fi, HTTP server, SNTP, etc. |
| **wolfSSH** | commit `157cb01f` | GPLv3 (or commercial) | SSH server protocol |
| **wolfSSL / wolfCrypt** | commit `b7e7e755` | GPLv3 (or commercial) | Cryptography library |
| ssd1306 | 0.8 | MIT / Apache-2.0 | OLED display driver |
| embedded-graphics | 0.8.1 | MIT / Apache-2.0 | Display rendering |
| @xterm/xterm | 6.0.0 (bundled) | MIT | Browser WebSocket terminal |
| @xterm/addon-fit | 0.11.0 (bundled) | MIT | xterm.js terminal fit addon |

> **Note on wolfSSH / wolfSSL licensing:**
> Both wolfSSH and wolfSSL are dual-licensed under **GPLv3** (open source) or a
> **commercial license** (for use in proprietary products).

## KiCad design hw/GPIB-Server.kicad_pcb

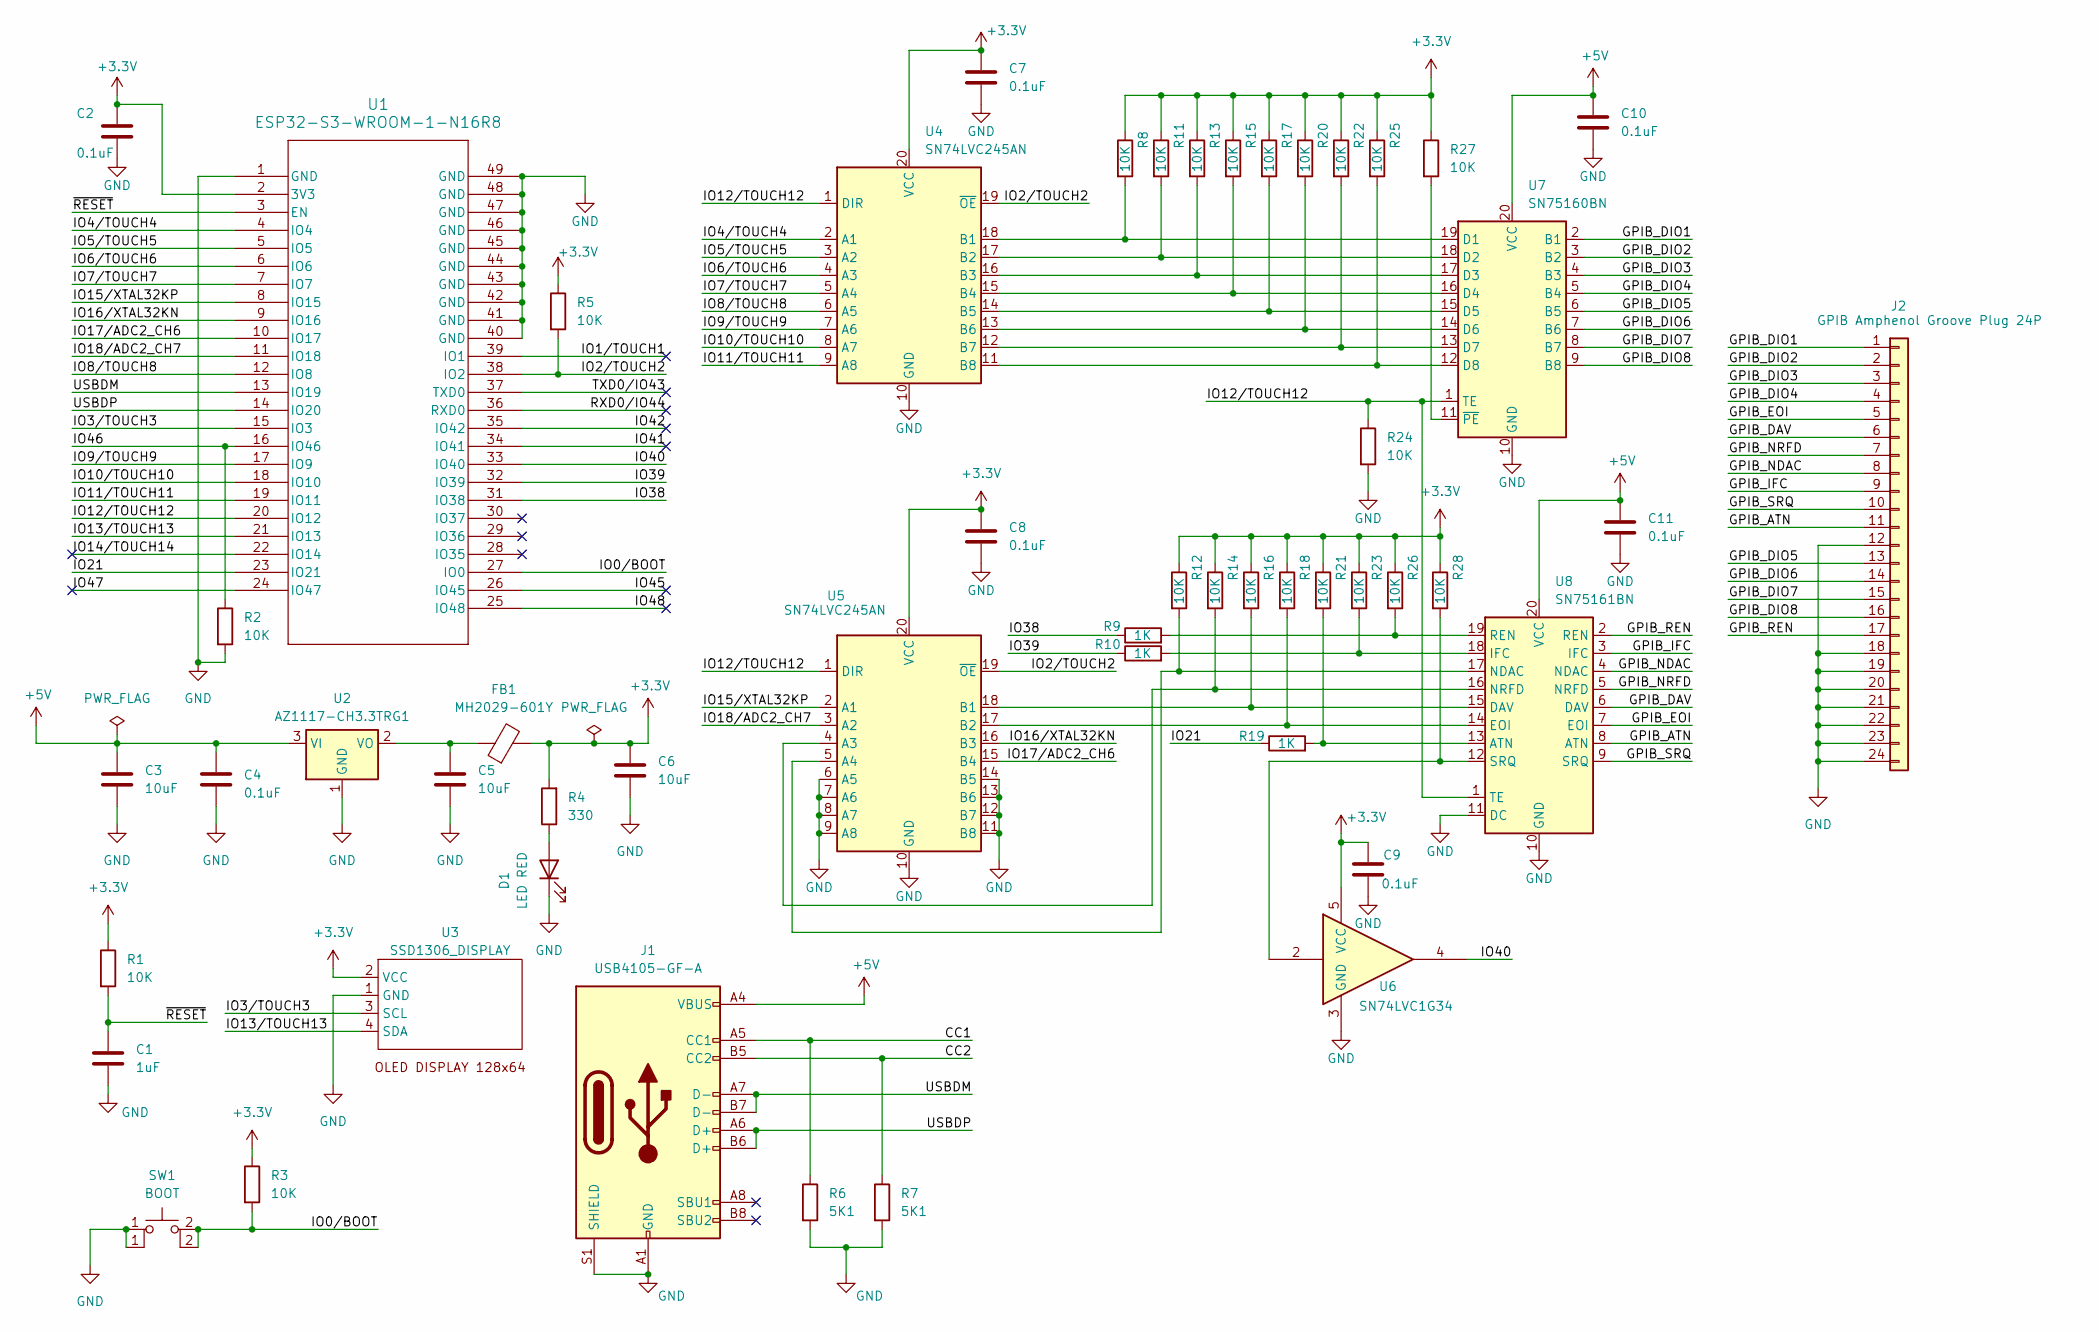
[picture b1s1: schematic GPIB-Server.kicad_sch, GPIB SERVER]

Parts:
C1: 1uF; C_0603_1608Metric; digikey 1276-6470-1-ND
C2, C4, C7, C8, C9, C10, C11: 0.1uF; C_0603_1608Metric; digikey 311-1344-1-ND
C3, C5, C6: 10uF; C_0805_2012Metric; digikey 1276-1096-1-ND
D1: LED RED; LED_0603_1608Metric; digikey 3147-B1931URO-20D000114U1930CT-ND
FB1: MH2029-601Y; L_0805_2012Metric; digikey MH2029-601YCT-ND
J1: USB4105-GF-A; USB_C_5077CR-16-SMC2-BK-TR; digikey 2073-USB4105-GF-ACT-ND
J2: GPIB Amphenol Groove Plug 24P; GPIB-MALE-PIN
R1, R2, R3, R5, R8, R11, R12, R13, R14, R15, R16, R17, R18, R20, R21, R22, R23, R24, R25, R26, R27, R28: 10K; R_0603_1608Metric; digikey 311-10.0KHRCT-ND
R4: 330; R_0603_1608Metric; digikey 13-RC0603JR-13330RLCT-ND
R6, R7: 5K1; R_0603_1608Metric; digikey 311-5.10KHRCT-ND
R9, R10, R19: 1K; R_0603_1608Metric; digikey 311-1.00KHRCT-ND
SW1: BOOT; SW_PUSH_6mm_H8mm; digikey 2223-TS02-66-70-BK-160-LCR-D-ND
U1: ESP32-S3-WROOM-1-N16R8; ESP32-S3-WROOM-1_EXP; digikey 1965-ESP32-S3-WROOM-1-N16R8CT-ND
U2: AZ1117-CH3.3TRG1; SOT-223-3_TabPin2; digikey AZ1117CH-3.3TRG1DICT-ND
U3: SSD1306_DISPLAY; OLED I2C DISPLAY
U4, U5: SN74LVC245AN; DIP-20_W7.62mm; digikey 296-8503-5-ND
U6: SN74LVC1G34; SOT-23-5; digikey 296-17893-1-ND
U7: SN75160BN; DIP-20_W7.62mm; digikey 296-6845-5-ND
U8: SN75161BN; DIP-20_W7.62mm; digikey 296-6847-5-ND

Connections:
+3.3V: C2.1, C6.1, C7.1, C8.1, C9.1, FB1.2, R1.1, R3.1, R4.2, R5.1, R8.1, R11.1, R12.1, R13.1, R14.1, R15.1, R16.1, R17.1, R18.1, R20.1, R21.1, R22.1, R23.1, R25.1, R26.1, R27.1, R28.1, U1.2 (3V3), U3.2 (VCC), U4.20 (VCC), U5.20 (VCC), U6.5 (VCC)
+5V: C3.1, C4.1, C10.1, C11.1, J1.A4 (VBUS), J1.A9 (VBUS), J1.B4 (VBUS), J1.B9 (VBUS), U2.3 (VI), U7.20 (VCC), U8.20 (VCC)
/CC1: J1.A5 (CC1), R6.1
/CC2: J1.B5 (CC2), R7.1
/GPIB_ATN: J2.11, U8.8 (ATN)
/GPIB_DAV: J2.6, U8.6 (DAV)
/GPIB_DIO1: J2.1, U7.2 (B1)
/GPIB_DIO2: J2.2, U7.3 (B2)
/GPIB_DIO3: J2.3, U7.4 (B3)
/GPIB_DIO4: J2.4, U7.5 (B4)
/GPIB_DIO5: J2.13, U7.6 (B5)
/GPIB_DIO6: J2.14, U7.7 (B6)
/GPIB_DIO7: J2.15, U7.8 (B7)
/GPIB_DIO8: J2.16, U7.9 (B8)
/GPIB_EOI: J2.5, U8.7 (EOI)
/GPIB_IFC: J2.9, U8.3 (IFC)
/GPIB_NDAC: J2.8, U8.4 (NDAC)
/GPIB_NRFD: J2.7, U8.5 (NRFD)
/GPIB_REN: J2.17, U8.2 (REN)
/GPIB_SRQ: J2.10, U8.9 (SRQ)
/IO0/BOOT: R3.2, SW1.2, U1.27 (IO0)
/IO1/TOUCH1: U1.39 (IO1)
/IO2/TOUCH2: R5.2, U1.38 (IO2), U4.19 (~OE), U5.19 (~OE)
/IO3/TOUCH3: U1.15 (IO3), U3.3 (SCL)
/IO4/TOUCH4: U1.4 (IO4), U4.2 (A1)
/IO5/TOUCH5: U1.5 (IO5), U4.3 (A2)
/IO6/TOUCH6: U1.6 (IO6), U4.4 (A3)
/IO7/TOUCH7: U1.7 (IO7), U4.5 (A4)
/IO8/TOUCH8: U1.12 (IO8), U4.6 (A5)
/IO9/TOUCH9: U1.17 (IO9), U4.7 (A6)
/IO10/TOUCH10: U1.18 (IO10), U4.8 (A7)
/IO11/TOUCH11: U1.19 (IO11), U4.9 (A8)
/IO12/TOUCH12: R24.1, U1.20 (IO12), U4.1 (DIR), U5.1 (DIR), U7.1 (TE), U8.1 (TE)
/IO13/TOUCH13: U1.21 (IO13), U3.4 (SDA)
/IO14/TOUCH14: U1.22 (IO14)
/IO15/XTAL32KP: U1.8 (IO15), U5.2 (A1)
/IO16/XTAL32KN: U1.9 (IO16), U5.16 (B3)
/IO17/ADC2_CH6: U1.10 (IO17), U5.15 (B4)
/IO18/ADC2_CH7: U1.11 (IO18), U5.3 (A2)
/IO21: R19.1, U1.23 (IO21)
/IO38: R9.1, U1.31 (IO38)
/IO39: R10.1, U1.32 (IO39)
/IO40: U1.33 (IO40), U6.4
/IO41: U1.34 (IO41)
/IO42: U1.35 (IO42)
/IO45: U1.26 (IO45)
/IO46: R2.1, U1.16 (IO46)
/IO47: U1.24 (IO47)
/IO48: U1.25 (IO48)
/RXD0/IO44: U1.36 (RXD0)
/TXD0/IO43: U1.37 (TXD0)
/USBDM: J1.A7 (D-), J1.B7 (D-), U1.13 (IO19)
/USBDP: J1.A6 (D+), J1.B6 (D+), U1.14 (IO20)
/~RESET: C1.1, R1.2, U1.3 (EN)
GND: C1.2, C2.2, C3.2, C4.2, C5.2, C6.2, C7.2, C8.2, C9.2, C10.2, C11.2, D1.1 (K), J1.A1 (GND), J1.A12 (GND), J1.B1 (GND), J1.B12 (GND), J1.S1 (SHIELD), J2.12, J2.18, J2.19, J2.20, J2.21, J2.22, J2.23, J2.24, R2.2, R6.2, R7.2, R24.2, SW1.1, U1.1 (GND), U1.40 (GND), U1.41 (GND), U1.42 (GND), U1.43 (GND), U1.44 (GND), U1.45 (GND), U1.46 (GND), U1.47 (GND), U1.48 (GND), U1.49 (GND), U2.1 (GND), U3.1 (GND), U4.10 (GND), U5.6 (A5), U5.7 (A6), U5.8 (A7), U5.9 (A8), U5.10 (GND), U5.11 (B8), U5.12 (B7), U5.13 (B6), U5.14 (B5), U6.3 (GND), U7.10 (GND), U8.10 (GND), U8.11 (DC)
unnamed: D1.2 (A), R4.1
unnamed: R10.2, R23.2, U8.18 (IFC)
unnamed: R19.2, R21.2, U8.13 (ATN)
unnamed: R9.2, R26.2, U8.19 (REN)
unnamed: R28.2, U6.2, U8.12 (SRQ)
unnamed: C5.1, FB1.1, U2.2 (VO)
unnamed: R8.2, U4.18 (B1), U7.19 (D1)
unnamed: R11.2, U4.17 (B2), U7.18 (D2)
unnamed: R13.2, U4.16 (B3), U7.17 (D3)
unnamed: R15.2, U4.15 (B4), U7.16 (D4)
unnamed: R17.2, U4.14 (B5), U7.15 (D5)
unnamed: R20.2, U4.13 (B6), U7.14 (D6)
unnamed: R22.2, U4.12 (B7), U7.13 (D7)
unnamed: R25.2, U4.11 (B8), U7.12 (D8)
unnamed: R14.2, U5.4 (A3), U8.16 (NRFD)
unnamed: R12.2, U5.5 (A4), U8.17 (NDAC)
unnamed: R16.2, U5.18 (B1), U8.15 (DAV)
unnamed: R18.2, U5.17 (B2), U8.14 (EOI)
unnamed: R27.2, U7.11 (~PE)

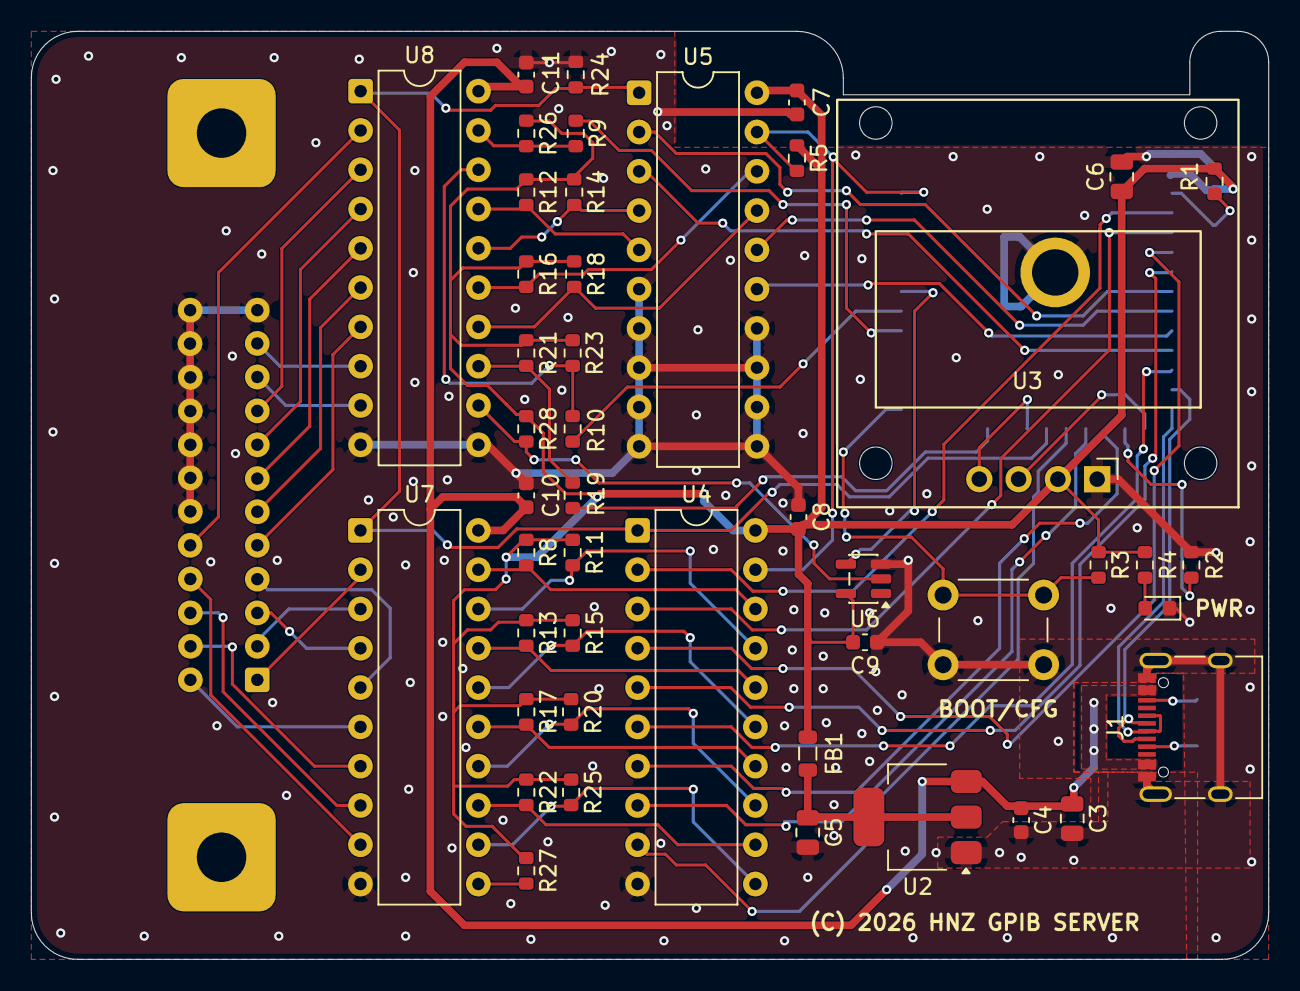
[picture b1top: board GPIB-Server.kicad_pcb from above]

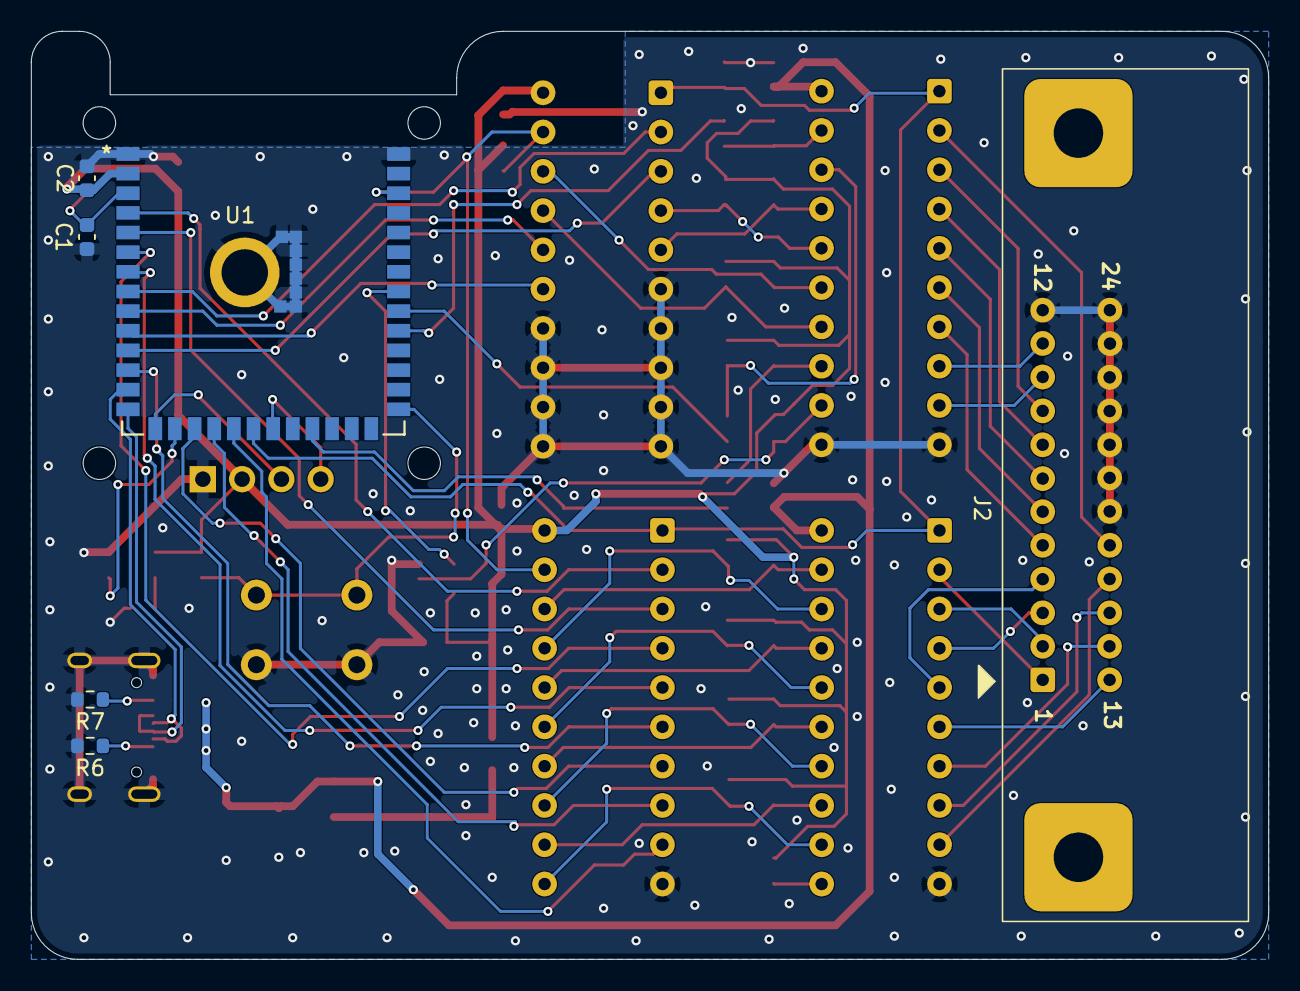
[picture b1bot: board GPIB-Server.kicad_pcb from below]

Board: 2 copper layers, 80.0 x 60.0 mm, 52 parts (6 on the bottom side), 65 nets.

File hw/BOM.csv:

"Reference","Qty","Value","Footprint","digikey/Other"
"C1","1","1uF","Capacitor_SMD:C_0603_1608Metric","1276-6470-1-ND"
"C2,C4,C7,C8,C9,C10,C11","7","0.1uF","Capacitor_SMD:C_0603_1608Metric","311-1344-1-ND"
"C3,C5,C6","3","10uF","Capacitor_SMD:C_0805_2012Metric","1276-1096-1-ND"
"D1","1","LED RED","LED_SMD:LED_0603_1608Metric","3147-B1931URO-20D000114U1930CT-ND"
"FB1","1","MH2029-601Y","Inductor_SMD:L_0805_2012Metric","MH2029-601YCT-ND"
"J1","1","USB4105-GF-A","Library:USB_C_5077CR-16-SMC2-BK-TR","2073-USB4105-GF-ACT-ND"
"J2","1","GPIB Amphenol Groove Plug 24P","Library:GPIB-MALE-PIN","https://ja.aliexpress.com/item/1005011562082439.html"
"R1,R2,R3,R5,R8,R11,R12,R13,R14,R15,R16,R17,R18,R20,R21,R22,R23,R24,R25,R26,R27,R28","22","10K","Resistor_SMD:R_0603_1608Metric","311-10.0KHRCT-ND"
"R4","1","330","Resistor_SMD:R_0603_1608Metric","13-RC0603JR-13330RLCT-ND"
"R6,R7","2","5K1","Resistor_SMD:R_0603_1608Metric","311-5.10KHRCT-ND"
"R9,R10,R19","3","1K","Resistor_SMD:R_0603_1608Metric","311-1.00KHRCT-ND"
"SW1","1","BOOT","Button_Switch_THT:SW_PUSH_6mm_H8mm","2223-TS02-66-70-BK-160-LCR-D-ND"
"U1","1","ESP32-S3-WROOM-1-N16R8","Library:ESP32-S3-WROOM-1_EXP","1965-ESP32-S3-WROOM-1-N16R8CT-ND"
"U2","1","AZ1117-CH3.3TRG1","Package_TO_SOT_SMD:SOT-223-3_TabPin2","AZ1117CH-3.3TRG1DICT-ND"
"U3","1","SSD1306_DISPLAY","Library:OLED I2C DISPLAY","https://ja.aliexpress.com/item/1005006141235306.html"
"U4,U5","2","SN74LVC245AN","Package_DIP:DIP-20_W7.62mm","296-8503-5-ND"
"U6","1","SN74LVC1G34","Package_TO_SOT_SMD:SOT-23-5","296-17893-1-ND"
"U7","1","SN75160BN","Package_DIP:DIP-20_W7.62mm","296-6845-5-ND"
"U8","1","SN75161BN","Package_DIP:DIP-20_W7.62mm","296-6847-5-ND"

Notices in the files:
hw/GPIB-Server.kicad_pcb:
(C) 2026 HNZ GPIB SERVER
hw/GPIB-Server.kicad_sch:
Licensed under CC-BY-SA V4.0
(C) 2026 Hiroshi Nakajima
